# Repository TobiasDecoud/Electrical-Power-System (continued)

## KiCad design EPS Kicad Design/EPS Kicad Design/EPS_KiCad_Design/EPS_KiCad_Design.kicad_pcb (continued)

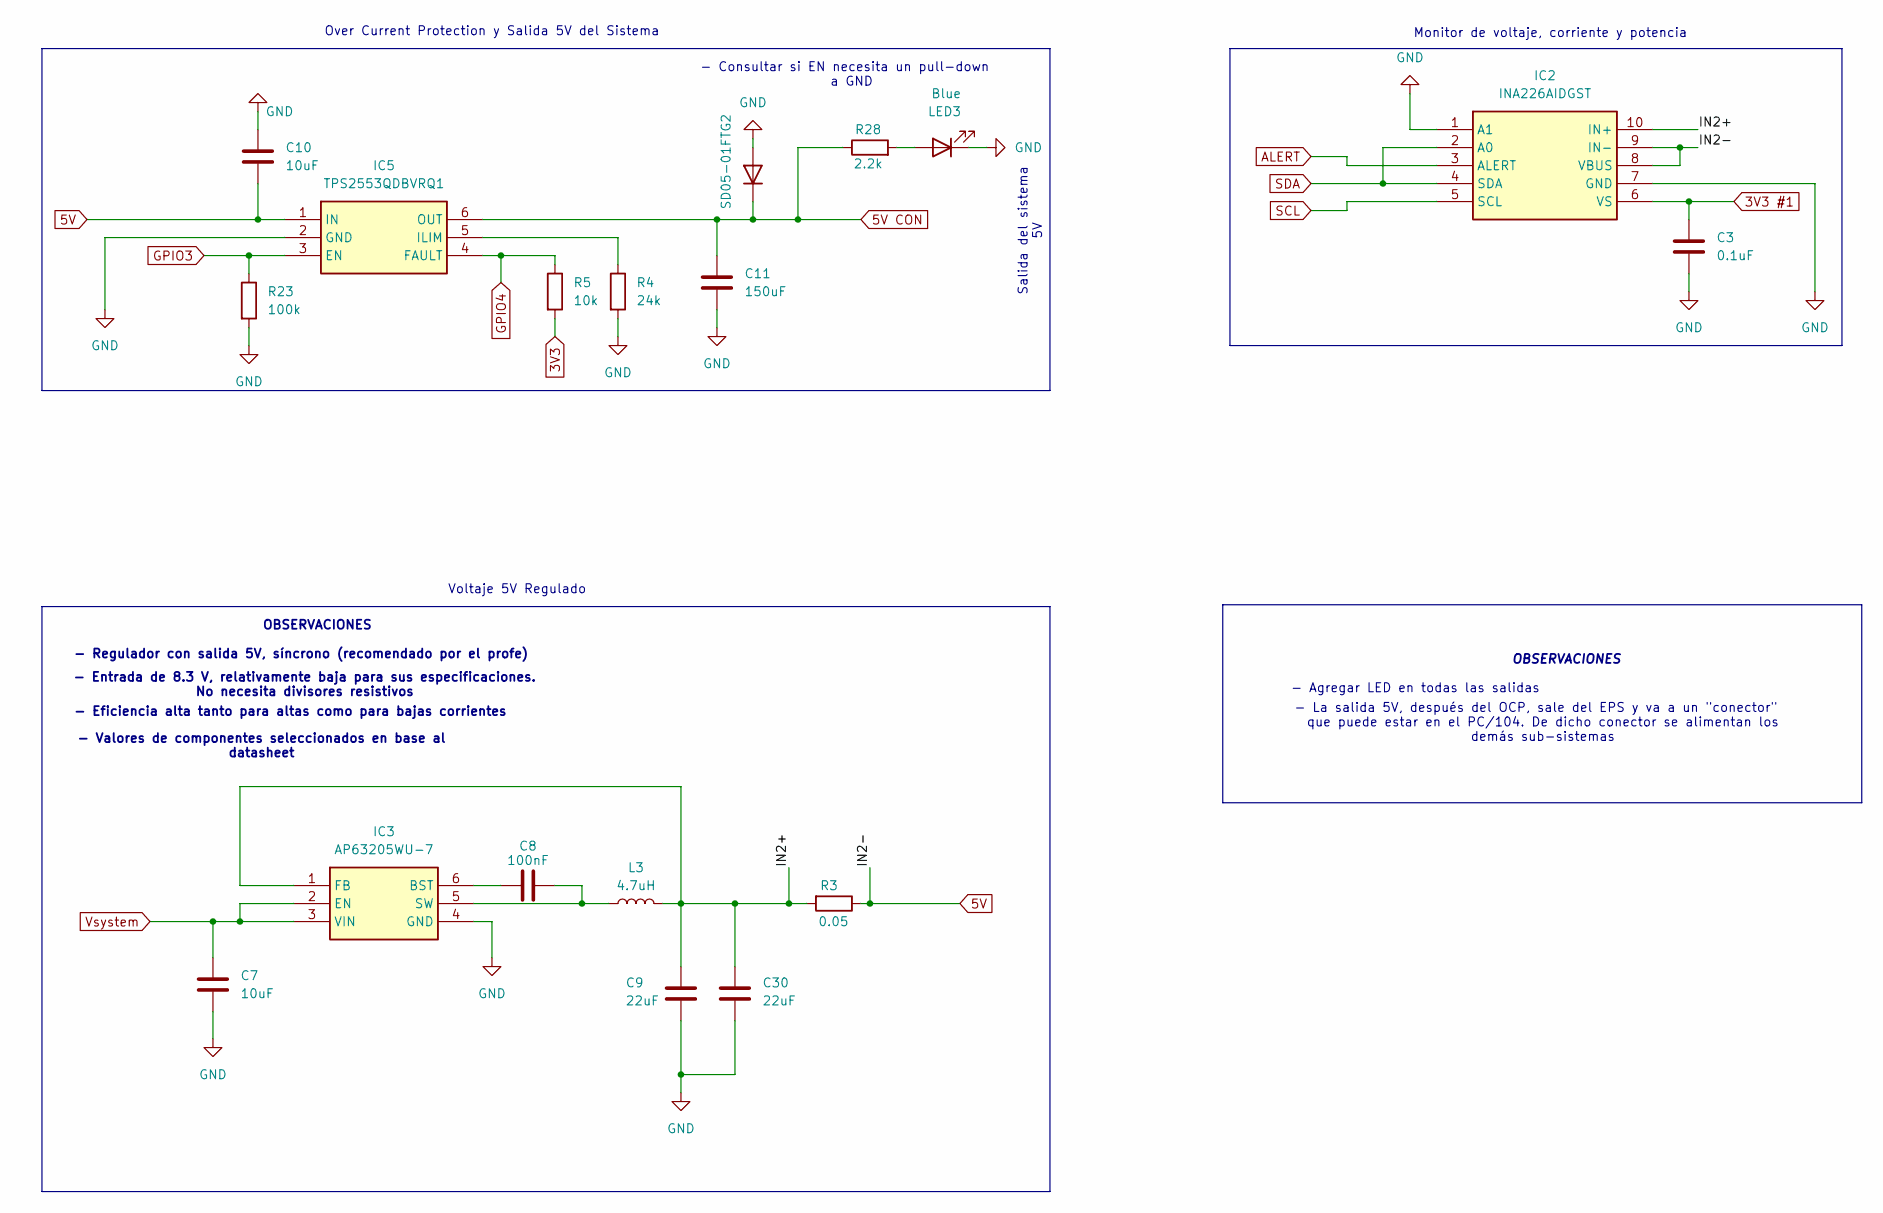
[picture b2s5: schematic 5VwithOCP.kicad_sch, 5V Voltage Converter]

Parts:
C3: 0.1uF; C_0805_2012Metric_Pad1.18x1.45mm_HandSolder
C7, C10: 10uF; C_0805_2012Metric_Pad1.18x1.45mm_HandSolder
C8: 100nF; C_0805_2012Metric_Pad1.18x1.45mm_HandSolder
C9, C30: 22uF; C_0805_2012Metric_Pad1.18x1.45mm_HandSolder
C11: 150uF; C_0805_2012Metric_Pad1.18x1.45mm_HandSolder
IC2: INA226AIDGST; SOP50P490X110-10N; Mouser Part Number 595-INA226AIDGST
IC3: AP63205WU-7; AP63205WU7; Mouser Part Number 621-AP63205WU-7
IC5: TPS2553QDBVRQ1; SOT95P280X145-6N; Mouser Part Number 595-TPS2553QDBVRQ1
L3: 4.7uH
LED3: Blue; LED_0805_2012Metric_Pad1.15x1.40mm_HandSolder
R3: 0.05; R_0805_2012Metric_Pad1.20x1.40mm_HandSolder
R4: 24k; R_0805_2012Metric_Pad1.20x1.40mm_HandSolder
R5: 10k; R_0805_2012Metric_Pad1.20x1.40mm_HandSolder
R23: 100k; R_0805_2012Metric_Pad1.20x1.40mm_HandSolder
R28: 2.2k; R_0805_2012Metric_Pad1.20x1.40mm_HandSolder
SD05-01FTG2: D; SOD2613X114N

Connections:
3V3: R5.2; also elsewhere on the board
3V3 #1: C3.1, IC2.6 (VS); also elsewhere on the board
5V: C10.2, IC2.8 (VBUS), IC2.9 (IN-), IC5.1 (IN), R3.1
5V CON: C11.1, IC5.6 (OUT), R28.1, SD05-01FTG2.1 (K); also elsewhere on the board
/Voltage Converter/5V + OCP/IN2+: C9.1, C30.1, IC2.10 (IN+), IC3.1 (FB), L3.2, R3.2
ALERT: IC2.3 (ALERT); also elsewhere on the board
GND: C3.2, C7.2, C9.2, C10.1, C11.2, C30.2, IC2.1 (A1), IC2.7 (GND), IC3.4 (GND), IC5.2 (GND), LED3.1 (K), R4.2, R23.2, SD05-01FTG2.2 (A); also elsewhere on the board
GPIO3: IC5.3 (EN), R23.1; also elsewhere on the board
GPIO4: IC5.4 (FAULT), R5.1; also elsewhere on the board
unnamed: C8.1, IC3.6 (BST)
unnamed: C8.2, IC3.5 (SW), L3.1
unnamed: IC5.5 (ILIM), R4.1
unnamed: LED3.2 (A), R28.2
SCL: IC2.5 (SCL); also elsewhere on the board
SDA: IC2.2 (A0), IC2.4 (SDA); also elsewhere on the board
Vsystem: C7.1, IC3.2 (EN), IC3.3 (VIN); also elsewhere on the board

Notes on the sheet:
- Consultar si EN necesita un pull-down a GND
Voltaje 5V Regulado
OBSERVACIONES
- Eficiencia alta tanto para altas como para bajas corrientes
- Agregar LED en todas las salidas
- Entrada de 8.3 V, relativamente baja para sus especificaciones. No necesita divisores resistivos
Salida del sistema 5V
- La salida 5V, después del OCP, sale del EPS y va a un "conector" que puede estar en el PC/104. De dicho conector se alimentan los demás sub-sistemas
- Valores de componentes seleccionados en base al datasheet
Over Current Protection y Salida 5V del Sistema
Monitor de voltaje, corriente y potencia
- Regulador con salida 5V, síncrono (recomendado por el profe)

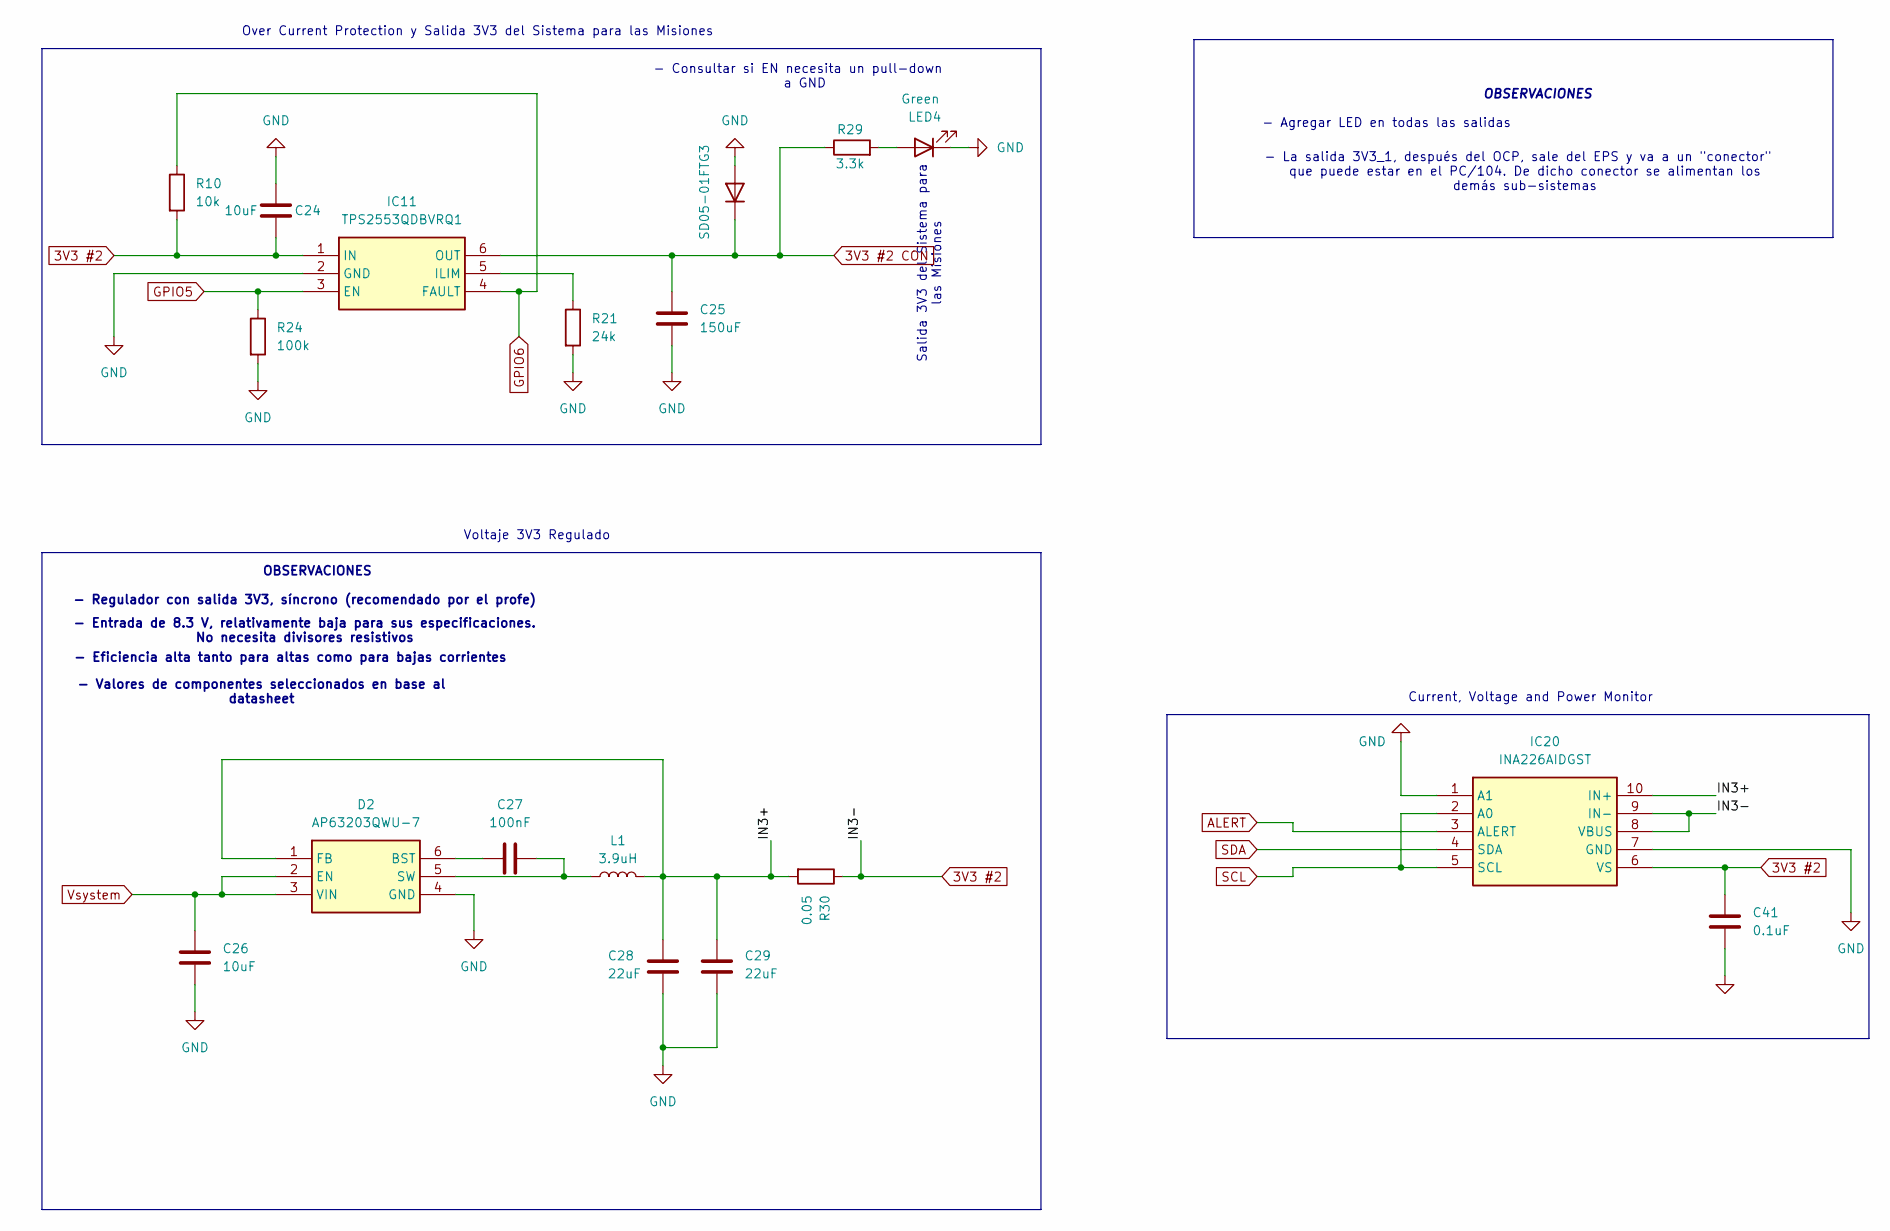
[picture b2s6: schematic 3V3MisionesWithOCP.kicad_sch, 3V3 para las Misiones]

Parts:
C24, C26: 10uF; C_0805_2012Metric_Pad1.18x1.45mm_HandSolder
C25: 150uF; C_0805_2012Metric_Pad1.18x1.45mm_HandSolder
C27: 100nF; C_0805_2012Metric_Pad1.18x1.45mm_HandSolder
C28, C29: 22uF; C_0805_2012Metric_Pad1.18x1.45mm_HandSolder
C41: 0.1uF; C_0805_2012Metric_Pad1.18x1.45mm_HandSolder
D2: AP63203QWU-7; SOT95P280X100-6N; Mouser Part Number 621-AP63203QWU-7
IC11: TPS2553QDBVRQ1; SOT95P280X145-6N; Mouser Part Number 595-TPS2553QDBVRQ1
IC20: INA226AIDGST; SOP50P490X110-10N; Mouser Part Number 595-INA226AIDGST
L1: 3.9uH
LED4: Green; LED_0805_2012Metric_Pad1.15x1.40mm_HandSolder
R10: 10k; R_0805_2012Metric_Pad1.20x1.40mm_HandSolder
R21: 24k; R_0805_2012Metric_Pad1.20x1.40mm_HandSolder
R24: 100k; R_0805_2012Metric_Pad1.20x1.40mm_HandSolder
R29: 3.3k; R_0805_2012Metric_Pad1.20x1.40mm_HandSolder
R30: 0.05; R_0805_2012Metric_Pad1.20x1.40mm_HandSolder
SD05-01FTG3: D; SOD2613X114N

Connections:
3V3 #2: C24.1, C41.1, IC11.1 (IN), IC20.6 (VS), IC20.8 (VBUS), IC20.9 (IN-), R10.2, R30.1
3V3 #2 CON: C25.1, IC11.6 (OUT), R29.1, SD05-01FTG3.1 (K); also elsewhere on the board
/Voltage Converter/3V3 Misiones + OCP/IN3+: C28.1, C29.1, D2.1 (FB), IC20.10 (IN+), L1.2, R30.2
ALERT: IC20.3 (ALERT); also elsewhere on the board
GND: C24.2, C25.2, C26.2, C28.2, C29.2, C41.2, D2.4 (GND), IC11.2 (GND), IC20.1 (A1), IC20.7 (GND), LED4.1 (K), R21.2, R24.2, SD05-01FTG3.2 (A); also elsewhere on the board
GPIO5: IC11.3 (EN), R24.1; also elsewhere on the board
GPIO6: IC11.4 (FAULT), R10.1; also elsewhere on the board
unnamed: C27.1, D2.6 (BST)
unnamed: C27.2, D2.5 (SW), L1.1
unnamed: IC11.5 (ILIM), R21.1
unnamed: LED4.2 (A), R29.2
SCL: IC20.2 (A0), IC20.5 (SCL); also elsewhere on the board
SDA: IC20.4 (SDA); also elsewhere on the board
Vsystem: C26.1, D2.2 (EN), D2.3 (VIN); also elsewhere on the board

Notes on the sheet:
OBSERVACIONES
- Eficiencia alta tanto para altas como para bajas corrientes
- Entrada de 8.3 V, relativamente baja para sus especificaciones. No necesita divisores resistivos
Voltaje 3V3 Regulado
- Regulador con salida 3V3, síncrono (recomendado por el profe)
- Agregar LED en todas las salidas
Current, Voltage and Power Monitor
- Valores de componentes seleccionados en base al datasheet
Salida 3V3 del Sistema para las Misiones
- Consultar si EN necesita un pull-down a GND
Over Current Protection y Salida 3V3 del Sistema para las Misiones
- La salida 3V3_1, después del OCP, sale del EPS y va a un "conector" que puede estar en el PC/104. De dicho conector se alimentan los demás sub-sistemas

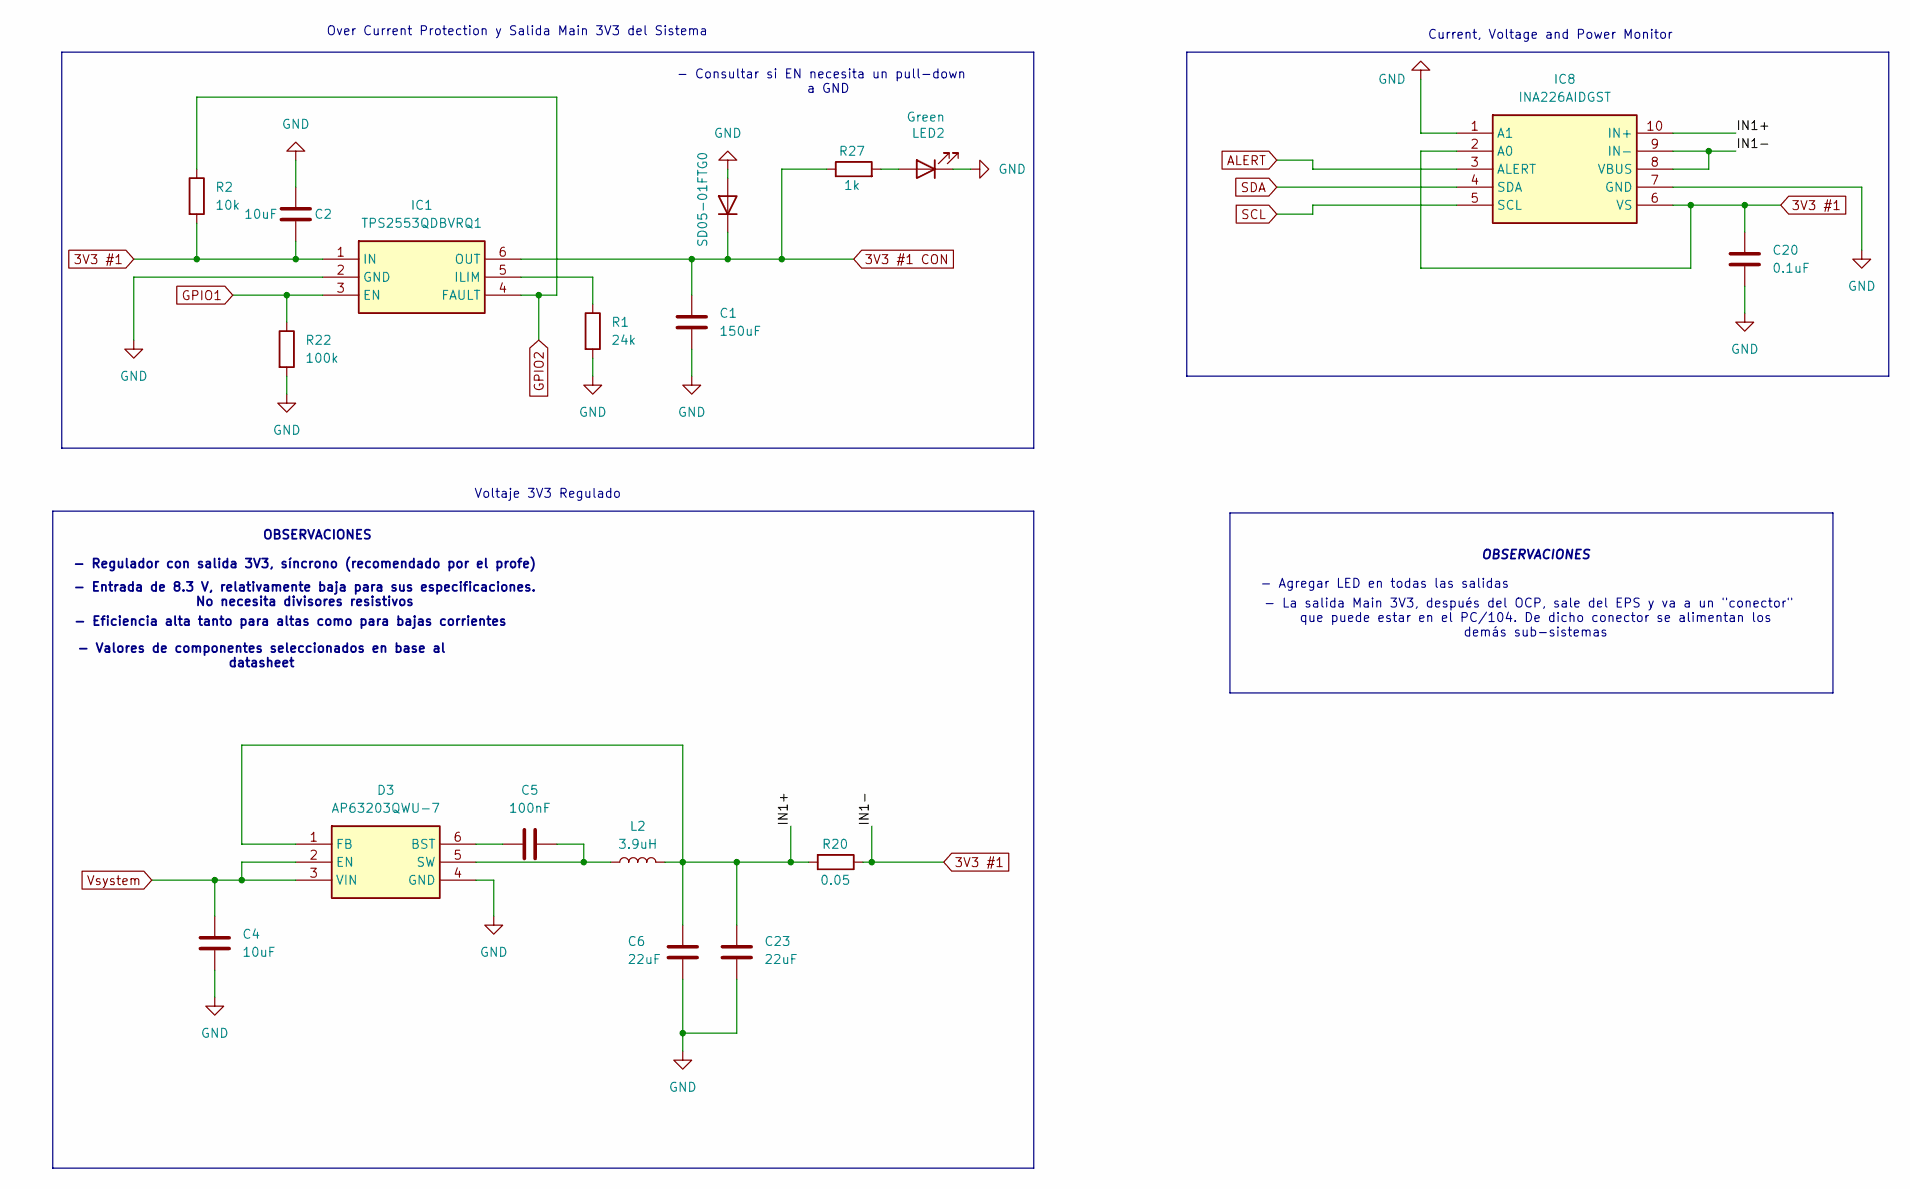
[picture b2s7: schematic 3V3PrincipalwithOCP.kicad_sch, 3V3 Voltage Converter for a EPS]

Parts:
C1: 150uF; C_0805_2012Metric_Pad1.18x1.45mm_HandSolder
C2, C4: 10uF; C_0805_2012Metric_Pad1.18x1.45mm_HandSolder
C5: 100nF; C_0805_2012Metric_Pad1.18x1.45mm_HandSolder
C6, C23: 22uF; C_0805_2012Metric_Pad1.18x1.45mm_HandSolder
C20: 0.1uF; C_0805_2012Metric_Pad1.18x1.45mm_HandSolder
D3: AP63203QWU-7; SOT95P280X100-6N; Mouser Part Number 621-AP63203QWU-7
IC1: TPS2553QDBVRQ1; SOT95P280X145-6N; Mouser Part Number 595-TPS2553QDBVRQ1
IC8: INA226AIDGST; SOP50P490X110-10N; Mouser Part Number 595-INA226AIDGST
L2: 3.9uH
LED2: Green; LED_0805_2012Metric_Pad1.15x1.40mm_HandSolder
R1: 24k; R_0805_2012Metric_Pad1.20x1.40mm_HandSolder
R2: 10k; R_0805_2012Metric_Pad1.20x1.40mm_HandSolder
R20: 0.05; R_0805_2012Metric_Pad1.20x1.40mm_HandSolder
R22: 100k; R_0805_2012Metric_Pad1.20x1.40mm_HandSolder
R27: 1k; R_0805_2012Metric_Pad1.20x1.40mm_HandSolder
SD05-01FTG0: D; SOD2613X114N

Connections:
3V3 #1: C2.1, C20.1, IC1.1 (IN), IC8.2 (A0), IC8.6 (VS), IC8.8 (VBUS), IC8.9 (IN-), R2.2, R20.1; also elsewhere on the board
3V3 #1 CON: C1.1, IC1.6 (OUT), R27.1, SD05-01FTG0.1 (K); also elsewhere on the board
/Voltage Converter/3V3 Principal + OCP/IN1+: C6.1, C23.1, D3.1 (FB), IC8.10 (IN+), L2.2, R20.2
ALERT: IC8.3 (ALERT); also elsewhere on the board
GND: C1.2, C2.2, C4.2, C6.2, C20.2, C23.2, D3.4 (GND), IC1.2 (GND), IC8.1 (A1), IC8.7 (GND), LED2.1 (K), R1.2, R22.2, SD05-01FTG0.2 (A); also elsewhere on the board
GPIO1: IC1.3 (EN), R22.1; also elsewhere on the board
GPIO2: IC1.4 (FAULT), R2.1; also elsewhere on the board
unnamed: C5.1, D3.6 (BST)
unnamed: C5.2, D3.5 (SW), L2.1
unnamed: IC1.5 (ILIM), R1.1
unnamed: LED2.2 (A), R27.2
SCL: IC8.5 (SCL); also elsewhere on the board
SDA: IC8.4 (SDA); also elsewhere on the board
Vsystem: C4.1, D3.2 (EN), D3.3 (VIN); also elsewhere on the board

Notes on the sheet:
- Consultar si EN necesita un pull-down a GND
Voltaje 3V3 Regulado
Current, Voltage and Power Monitor
- Entrada de 8.3 V, relativamente baja para sus especificaciones. No necesita divisores resistivos
- Regulador con salida 3V3, síncrono (recomendado por el profe)
- Eficiencia alta tanto para altas como para bajas corrientes
OBSERVACIONES
- Valores de componentes seleccionados en base al datasheet
Over Current Protection y Salida Main 3V3 del Sistema
- Agregar LED en todas las salidas
- La salida Main 3V3, después del OCP, sale del EPS y va a un "conector" que puede estar en el PC/104. De dicho conector se alimentan los demás sub-sistemas

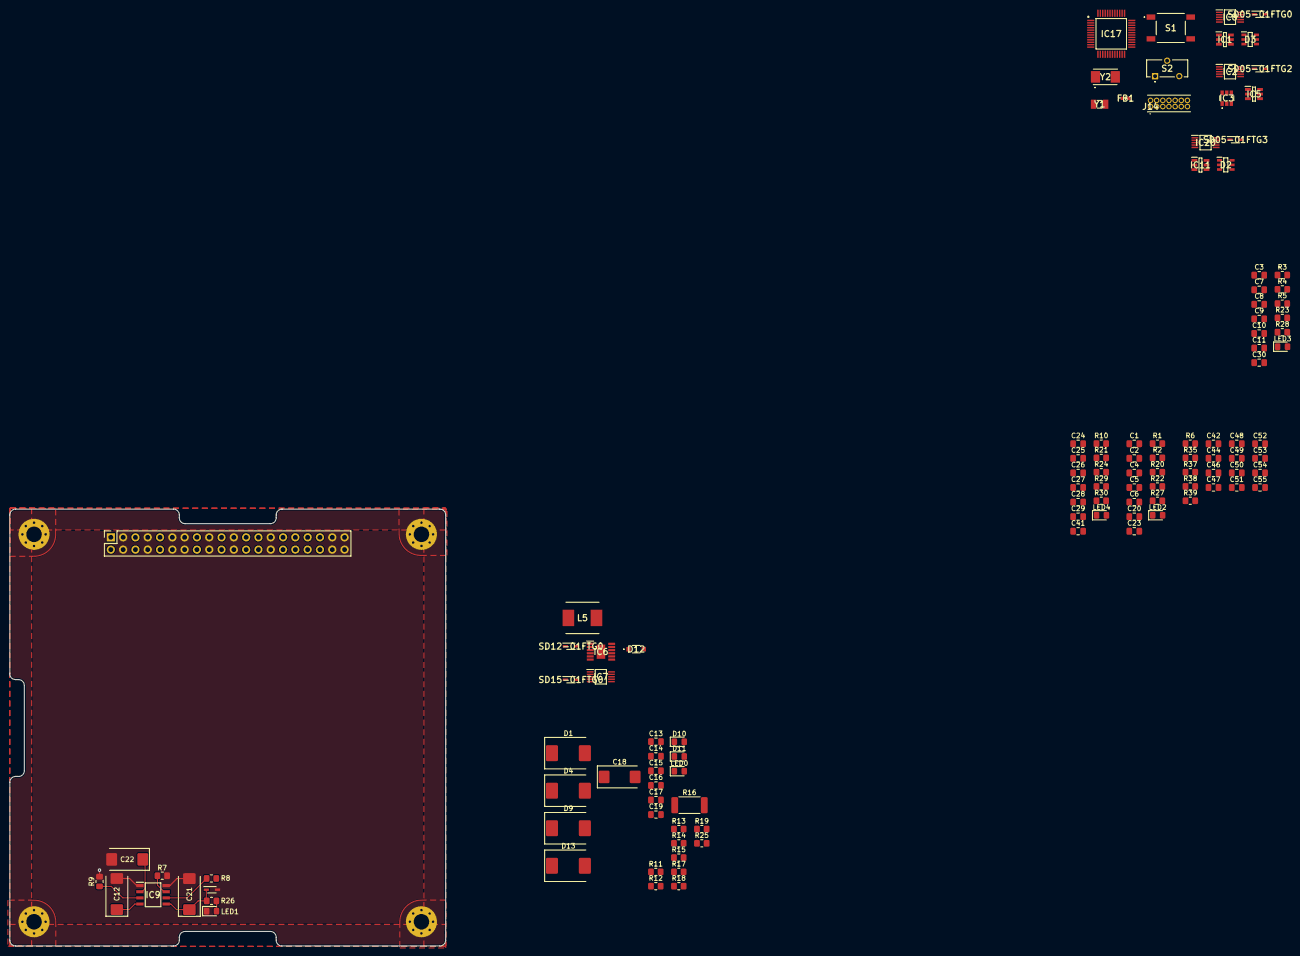
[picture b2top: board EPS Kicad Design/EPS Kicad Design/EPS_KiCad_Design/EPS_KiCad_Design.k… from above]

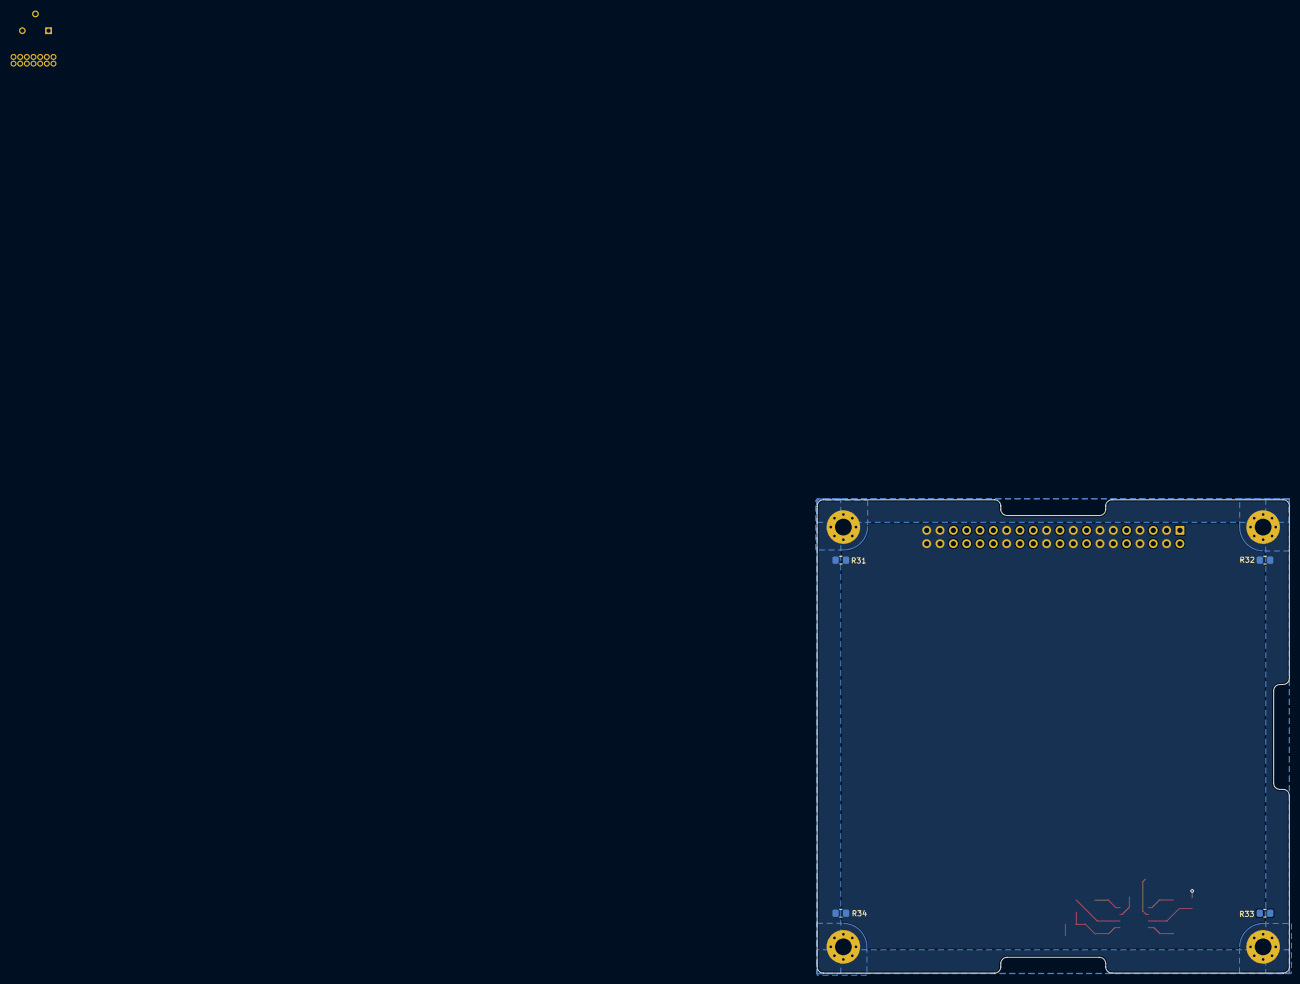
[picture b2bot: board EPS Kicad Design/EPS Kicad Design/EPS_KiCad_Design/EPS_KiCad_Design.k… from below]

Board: 4 copper layers, 90.0 x 90.2 mm, 124 parts (4 on the bottom side), 73 nets.

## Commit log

2026-02-22 Actualizacion de README
2026-02-22 Actualizar EPS DIAGRAMA.drawio.svg
2026-02-24 Source - Papers
2026-02-25 Inicio PCB
2026-03-03 actualizacion pcb¨
2026-03-09 Main PCB - EPS
2026-03-29 Agregue PBS y nuevo Diagrama
2026-03-29 Cambio en el diagrama
2026-03-29 Cambie ubicacion de baterry en el diagrama
2026-03-30 Actualizar diagrama.svg
2026-04-15 Actualizacion del PCB en Kicad
2026-04-15 actualizacion
2026-04-20 cargue pcb
2026-04-27 pcb tobi
2026-04-27 Ruteo parcial de MCU
2026-04-28 Agregue cosas al ruteo MCU
2026-04-28 Correcciones MCU ruteo
2026-04-28 RUTEO MCU
2026-04-28 Correccion de STP de los cristales
2026-04-28 Cambios menores
2026-04-29 Actualizacion del PCB
2026-04-30 Cambio de conector
    Conector header de 5 posiciones
2026-05-02 Estapadines agregados en el diseño
2026-05-02 cambios en el ruteo
2026-05-03 Cambios pcb
2026-05-03 cambios minimos para pasar el DFM Checker
2026-05-03 JLC specificaction pdf
2026-05-04 Agrege nombres visibles a PC104
2026-05-04 anhadi el fabrication file
2026-05-05 actualizacion del fabrication files
2026-05-06 Agregue nombres al pcb
2026-05-24 Diagrama de Flujo
2026-05-25 Agregue DF final
